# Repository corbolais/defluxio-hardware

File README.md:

Hardware for the netzsinus project
===================================

This repository contains the measurement hardware and firmware of the
netzsinus project. The current hardware is still under development -
you have to solder your own hardware. The hardware is, however, pretty
simple and easy to build.

Our vision is to develop a network analyzer in the sense of [DIN EN
50160](https://de.wikipedia.org/wiki/EN_50160). Currently, only the
network frequency is measured, but other measurements such as voltage
and harmonics will be included step-by-step.

Overview
--------

The hardware consists of

* A 9VAC wall-wart power adaptor. I have only tested Ideal Power model
DE-06-09, but others should also work.
* A STM32F4 Discovery board. This evaluation kit offers a Cortex M4
microcontroller which will become handy if we implement the harmonics
analysis.
* An adapter board which contains the analog frondend and connects all
the components.
* A raspberry pi which runs a simple Go daemon to read the data from the
hardware and transmit it to https://netzsin.us.

The current design powers the STM32F4 from the Raspberry Pi. It would also 
be possible to power the system from the 9VAC power adaptor, but initial 
experiments showed distorsions in the sine wave caused by the bridge rectifier.
A precision bridge rectifier setup could solve this.

Building your own device
------------------------

Currently, you just have to solder your own hardware. But since the
hardware is pretty simple this is an easy task. Please use this
schematic:

The opamp is an TLC393 comparator. I used a protoboard and THT components to build this circuit as a shield
for the STM32F4 discovery board. This is my setup:

The STM32F4 discovery costs around 15 Euro, the 9VAC adaptor around 5,
everything else maybe 2 Euros.

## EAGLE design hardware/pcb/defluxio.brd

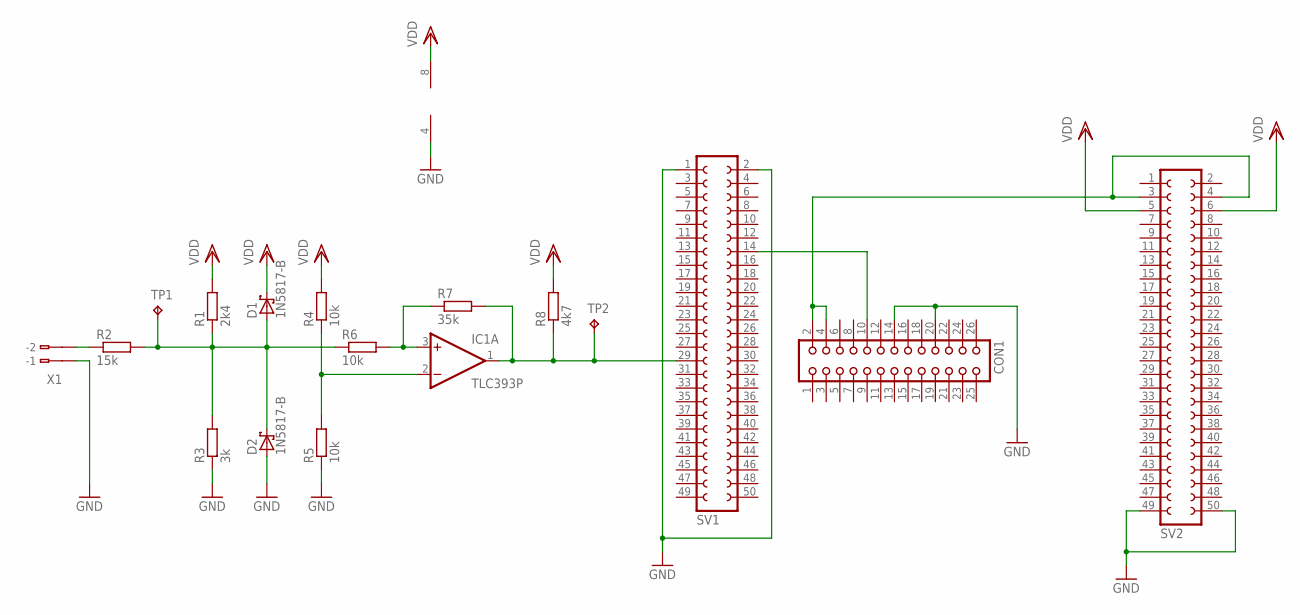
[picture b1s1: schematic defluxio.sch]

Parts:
CON1: CON26
D1, D2: 1N5817-B; DO41-7.6
IC1: TLC393P; DIL08
R1: 2k4; 0204/7
R2: 15k; 0207/12
R3: 3k; 0207/15
R4: 10k; 0207/12
R5: 10k; 0207/10
R6: 10k; 0204/7
R7: 35k; 0207/10
R8: 4k7; 0207/10
SV1, SV2: FE25-2
TP1, TP2: TPPAD1-13; P1-13
X1: 233-102

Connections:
5V: CON1.2, CON1.4, SV2.3, SV2.4
GND: CON1.14, CON1.20, D2.A, IC1.4 (V-), R3.1, R5.1, SV1.1, SV1.2, SV2.49, SV2.50, X1.B1 (B-1)
unnamed: R2.1, X1.B2 (B-2)
unnamed: IC1.3 (+IN), R6.2, R7.1
unnamed: IC1.2 (-IN), R4.1, R5.2
PE11: IC1.1 (OUT), R7.2, R8.1, SV1.29, TP2.TP
RX: CON1.10, SV1.14
SIG: D1.A, D2.C, R1.1, R2.2, R3.2, R6.1, TP1.TP
VDD: D1.C, IC1.8 (V+), R1.2, R4.2, R8.2, SV2.5, SV2.6

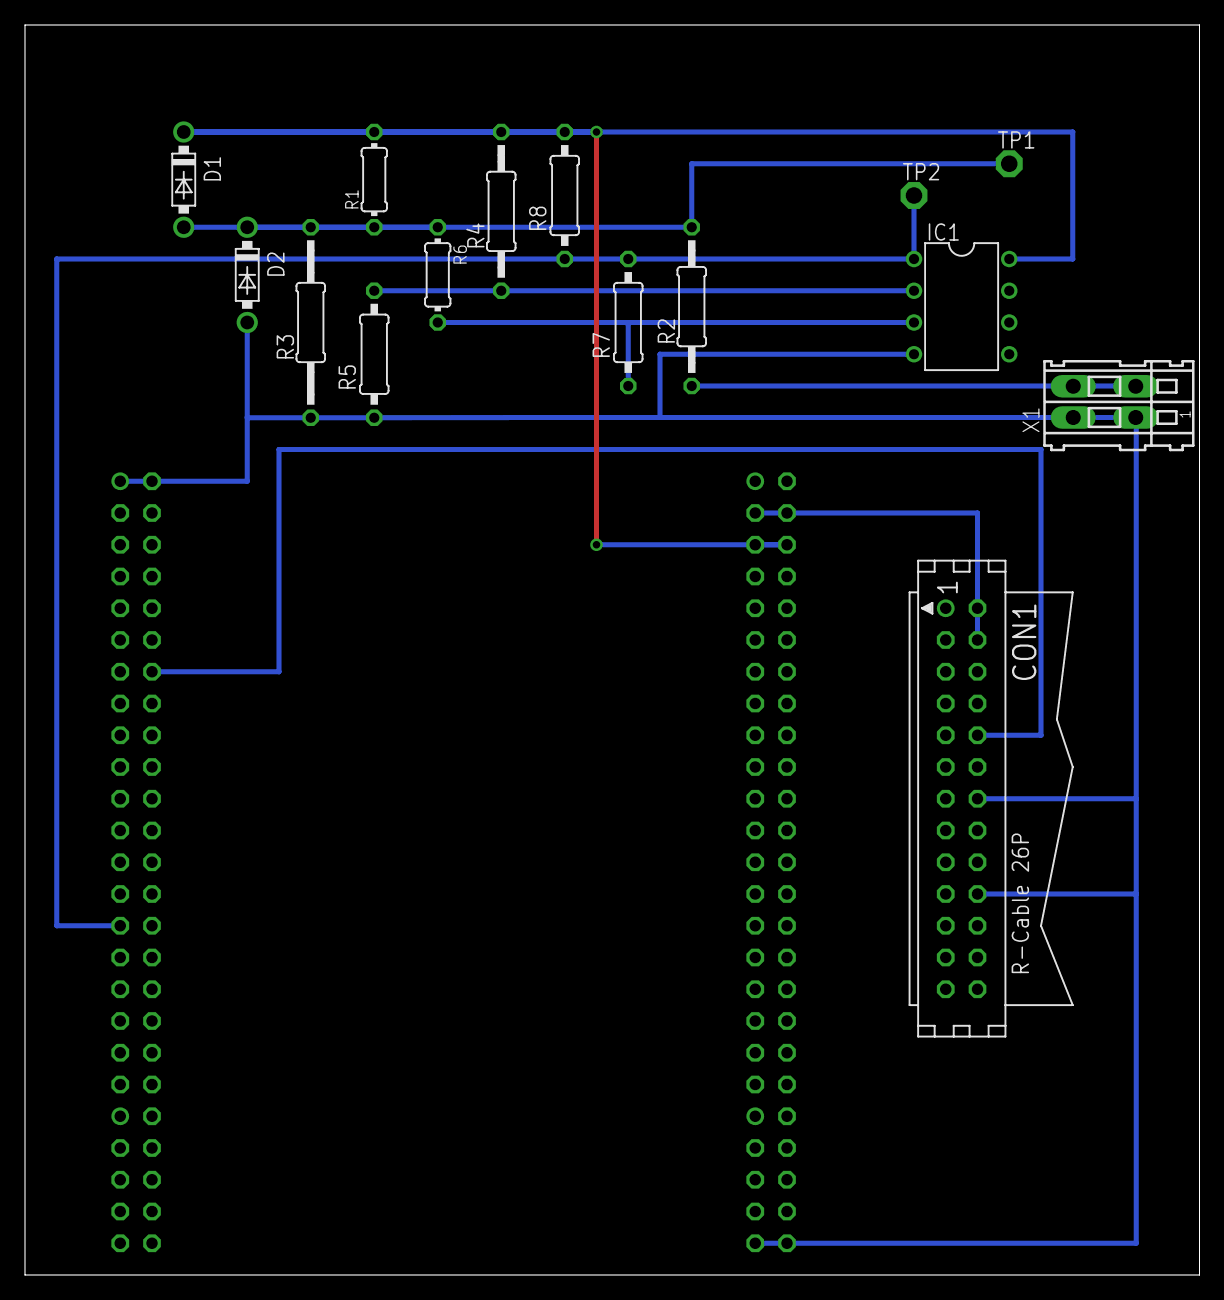
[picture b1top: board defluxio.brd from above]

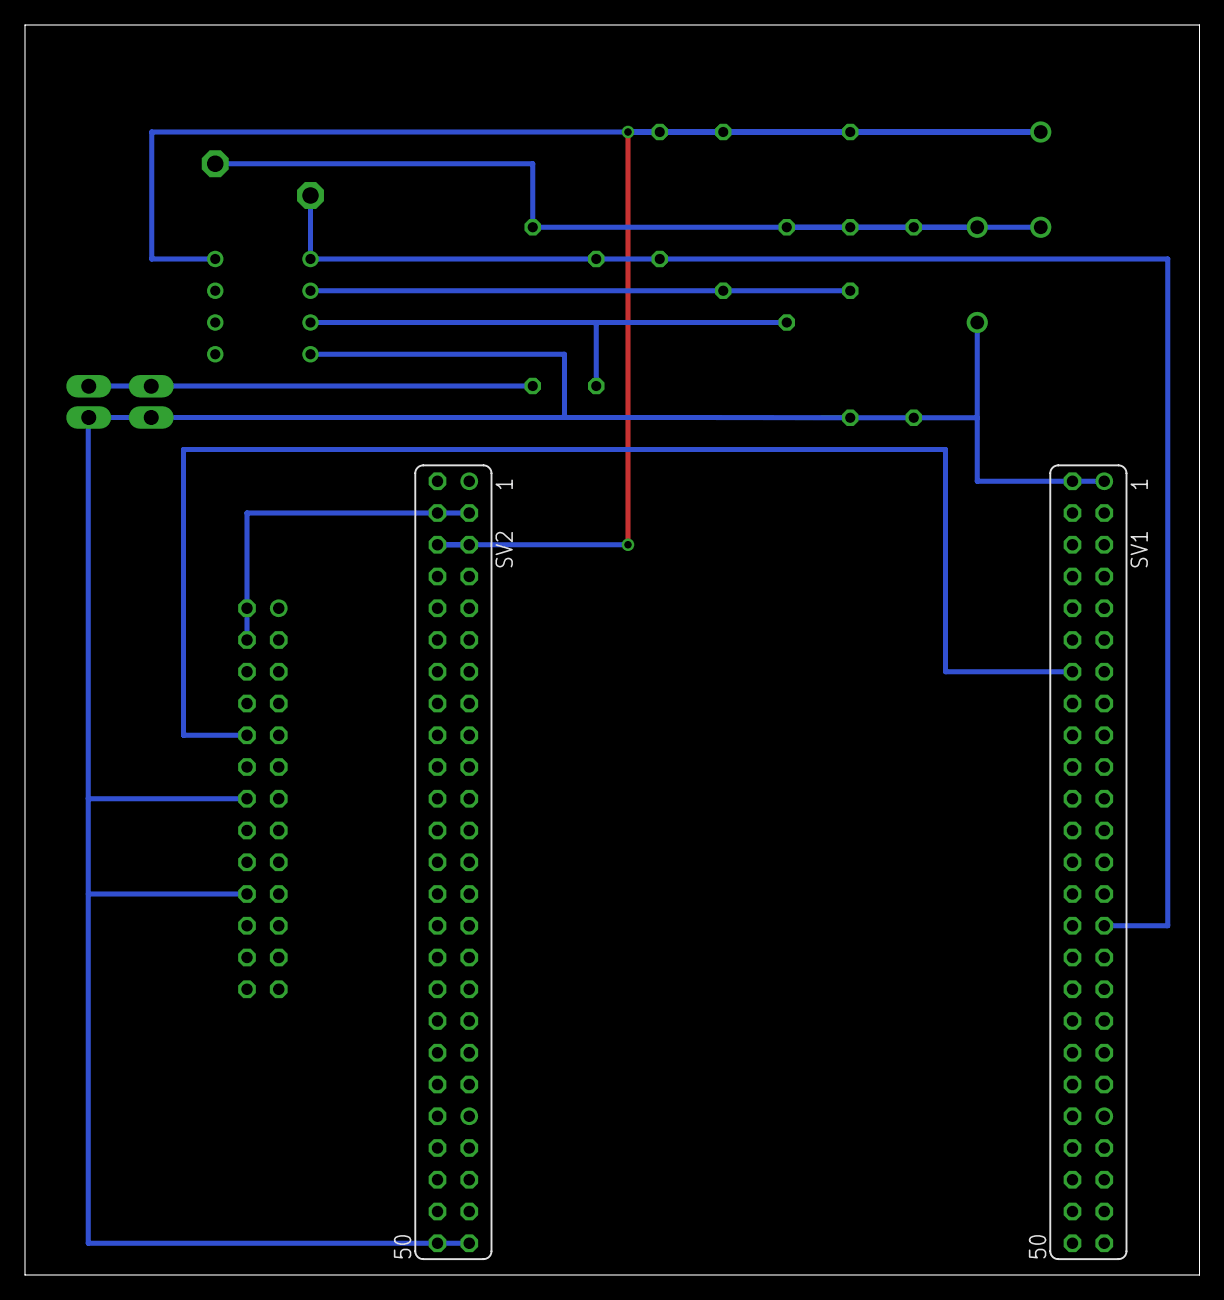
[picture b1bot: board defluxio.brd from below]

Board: 2 copper layers, 94.0 x 100.0 mm, 17 parts (2 on the bottom side), 9 nets.

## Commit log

2014-08-15 moved stuff around
2014-08-15 the license should be in the top-level directory
2014-08-19 input capture infrastructure is working, but overflow handling is broken.
2014-08-21 structure of code is ok, but values are not plausible
2014-08-21 tracking overcapture events.
2014-08-22 frequency calculation now accurate
2014-08-22 refactored and added defluxio log formatter for compatibility
2014-09-01 added pics of v0.2 hardware
2014-09-01 added readme
2014-09-01 exchanged boilerplate build information with project-specific ones
2014-09-02 TLC393 hint added
2014-09-02 power design background
2015-03-10 typo
2015-10-30 added EAGLE PCB (first draft) from schematics in pics directory
2020-10-11 CJMCU: make built-in LED on PE0 blink
